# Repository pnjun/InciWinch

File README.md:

# InciWinch

A feedback system for glider winch launches - Akaflieg Berlin

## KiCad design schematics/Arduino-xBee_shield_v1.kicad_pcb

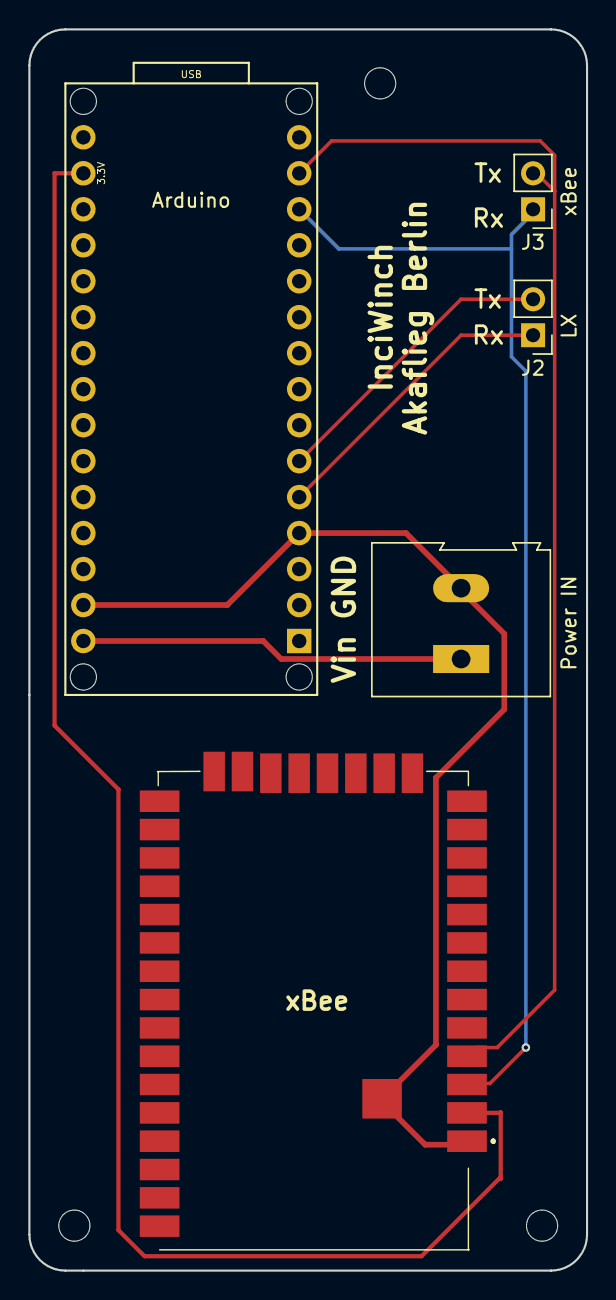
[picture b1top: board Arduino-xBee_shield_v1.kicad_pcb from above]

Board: 2 copper layers, 39.4 x 87.6 mm, 5 parts (0 on the bottom side), 7 nets.

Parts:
Arduino: Arduino_Nano_Socket
J2: LX; Socket_Strip_Straight_1x02_Pitch2.54mm
J3: xBee; Socket_Strip_Straight_1x02_Pitch2.54mm
Power IN: Power In; TerminalBlock_Altech_AK300-2_P5.00mm
xBee: xBee SX 868; XBP9XDMRS001

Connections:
unnamed: Arduino.3V3, xBee.2
unnamed: Arduino.D2, J2.1
unnamed: Arduino.D3, J2.2
unnamed: Arduino.D10, J3.1, xBee.3
unnamed: Arduino.D11, J3.2, xBee.4
unnamed: Arduino.GND1, Arduino.GND2, Power IN.2, xBee.1, xBee.38
unnamed: Arduino.VIN, Power IN.1

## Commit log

2018-02-11 TODO and links
2018-02-22 links to xBee manuals and tutorials
2018-03-16 python library API test
2018-03-29 Arduino NMEA decoder (and gcc compilable test version)
2018-03-29 .cpp fix
2018-04-18 arduino serial relay
2018-04-22 Arduino-xBee API comms with generation of fake data
2018-04-22 python code to receive data from arduino
2018-04-24 kivy user interface first code
2018-04-24 RadioHandler is now a class
2018-04-25 Moving code around files
2018-04-25 radio frames queue and callbacks
2018-04-25 display of flight data in appropriate launchtabs
2018-05-23 Added fakedata generator and real time data plotting to winch side app
2018-06-03 bug fixes + schematics start
2018-06-09 schematics and PCB design
2018-06-24 gerber files
2018-06-24 code cleanup + launch save&close buttons
2018-07-15 moved folders
2018-07-15 code for fakedata with SX868
2018-07-15 bug fix and moving files around
2018-07-15 trying to remove folders
2018-07-15 more folders
